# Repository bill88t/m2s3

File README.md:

# m2s3
A ESP32-S3 M.2 B-Key board that can be controller over host USB.

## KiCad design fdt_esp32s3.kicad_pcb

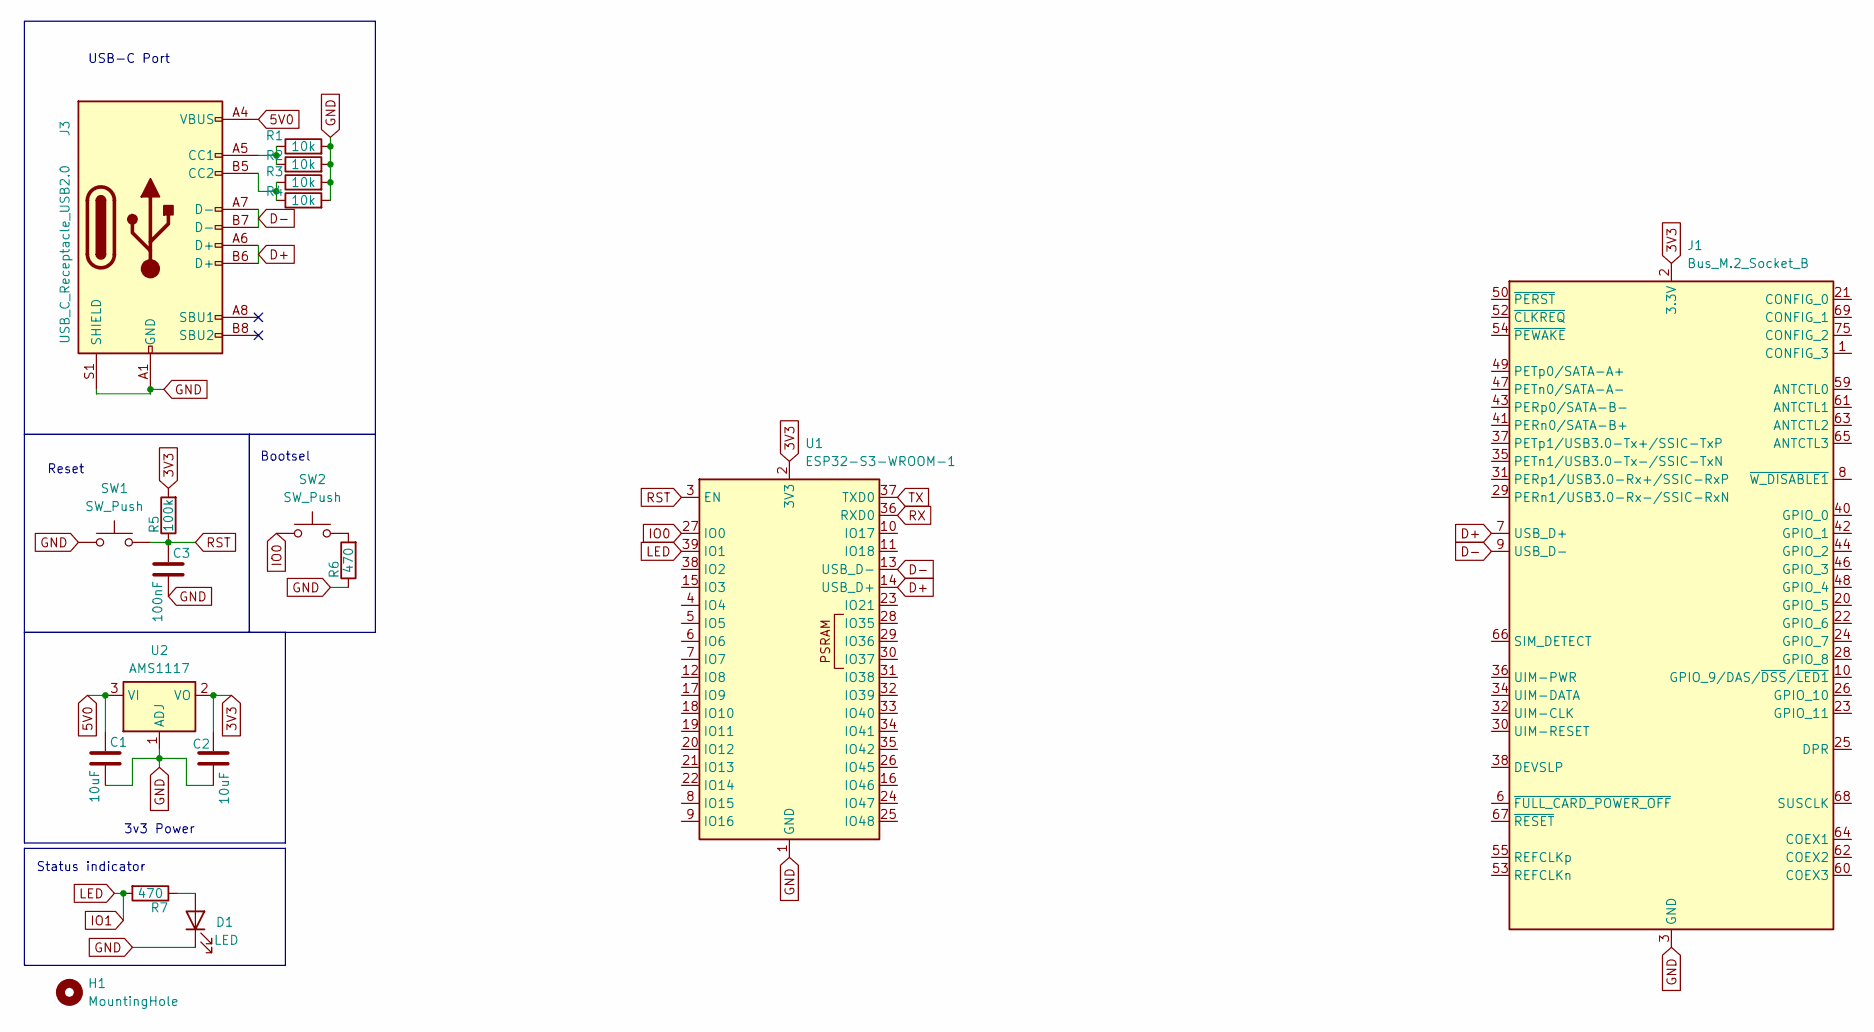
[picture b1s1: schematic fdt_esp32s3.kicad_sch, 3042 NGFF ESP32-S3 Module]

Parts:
C1, C2: 10uF; C_0805_2012Metric_Pad1.18x1.45mm_HandSolder
C3: 100nF; C_0805_2012Metric_Pad1.18x1.45mm_HandSolder
D1: LED; LED_1206_3216Metric_Pad1.42x1.75mm_HandSolder
H1: MountingHole; m2-outer2230
J1: Bus_M.2_Socket_B; m2-padKeyB
J3: USB_C_Receptacle_USB2.0; USB_C_Receptacle_G-Switch_GT-USB-7010ASV
R1, R2, R3, R4: 10k; R_0805_2012Metric_Pad1.20x1.40mm_HandSolder
R5: 100k; R_0805_2012Metric_Pad1.20x1.40mm_HandSolder
R6, R7: 470; R_0805_2012Metric_Pad1.20x1.40mm_HandSolder
SW1, SW2: SW_Push; SW_Push_1P1T_NO_CK_KMR2
U1: ESP32-S3-WROOM-1
U2: AMS1117; SOT-223

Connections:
3V3: C2.1, J1.2 (3.3V), J1.4 (3.3V), J1.70 (3.3V), J1.72 (3.3V), J1.74 (3.3V), R5.2, U1.2 (3V3), U2.2 (VO)
5V0: C1.1, J3.A4 (VBUS), J3.A9 (VBUS), J3.B4 (VBUS), J3.B9 (VBUS), U2.3 (VI)
D+: J1.7 (USB_D+), J3.A6 (D+), J3.B6 (D+), U1.14 (USB_D+)
D-: J1.9 (USB_D-), J3.A7 (D-), J3.B7 (D-), U1.13 (USB_D-)
GND: C1.2, C2.2, C3.2, D1.1 (K), J1.3 (GND), J1.5 (GND), J1.11 (GND), J1.27 (GND), J1.33 (GND), J1.39 (GND), J1.45 (GND), J1.51 (GND), J1.57 (GND), J1.71 (GND), J1.73 (GND), J3.A1 (GND), J3.A12 (GND), J3.B1 (GND), J3.B12 (GND), J3.S1 (SHIELD), R1.2, R2.2, R3.2, R4.2, R6.1, SW1.1, U1.1 (GND), U1.40 (GND), U2.1 (ADJ)
IO0: SW2.1, U1.27 (IO0)
IO1: R7.2, U1.39 (IO1)
unnamed: D1.2 (A), R7.1
unnamed: J3.A5 (CC1), R1.1, R2.1
unnamed: J3.B5 (CC2), R3.1, R4.1
unnamed: R6.2, SW2.2
RST: C3.1, R5.1, SW1.2, U1.3 (EN)
RX: U1.36 (RXD0)
TX: U1.37 (TXD0)

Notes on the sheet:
Reset
3v3 Power
Bootsel
Status indicator
USB-C Port

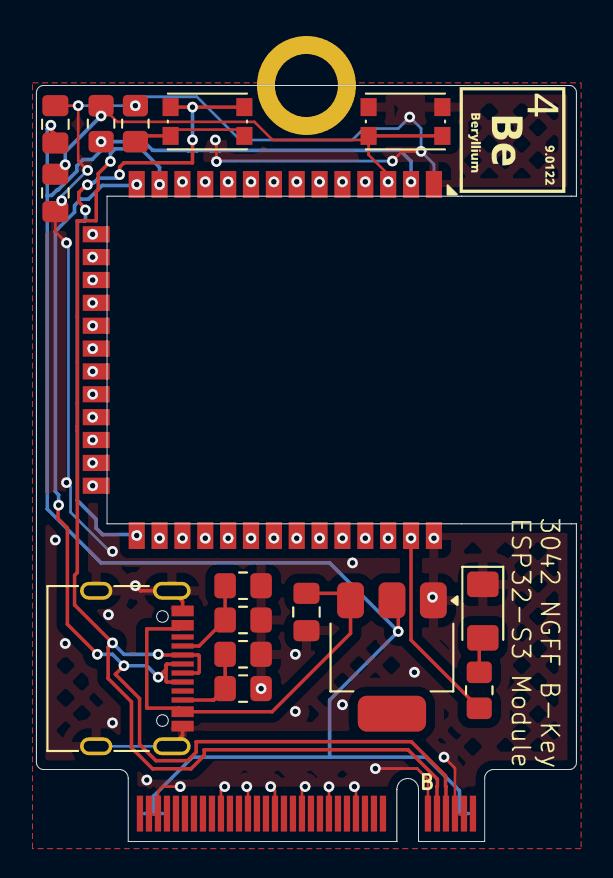
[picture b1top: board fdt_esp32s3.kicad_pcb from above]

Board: 2 copper layers, 30.0 x 42.0 mm, 18 parts (0 on the bottom side), 12 nets.

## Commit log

2025-04-07 Initial add
2025-04-07 Add licence
